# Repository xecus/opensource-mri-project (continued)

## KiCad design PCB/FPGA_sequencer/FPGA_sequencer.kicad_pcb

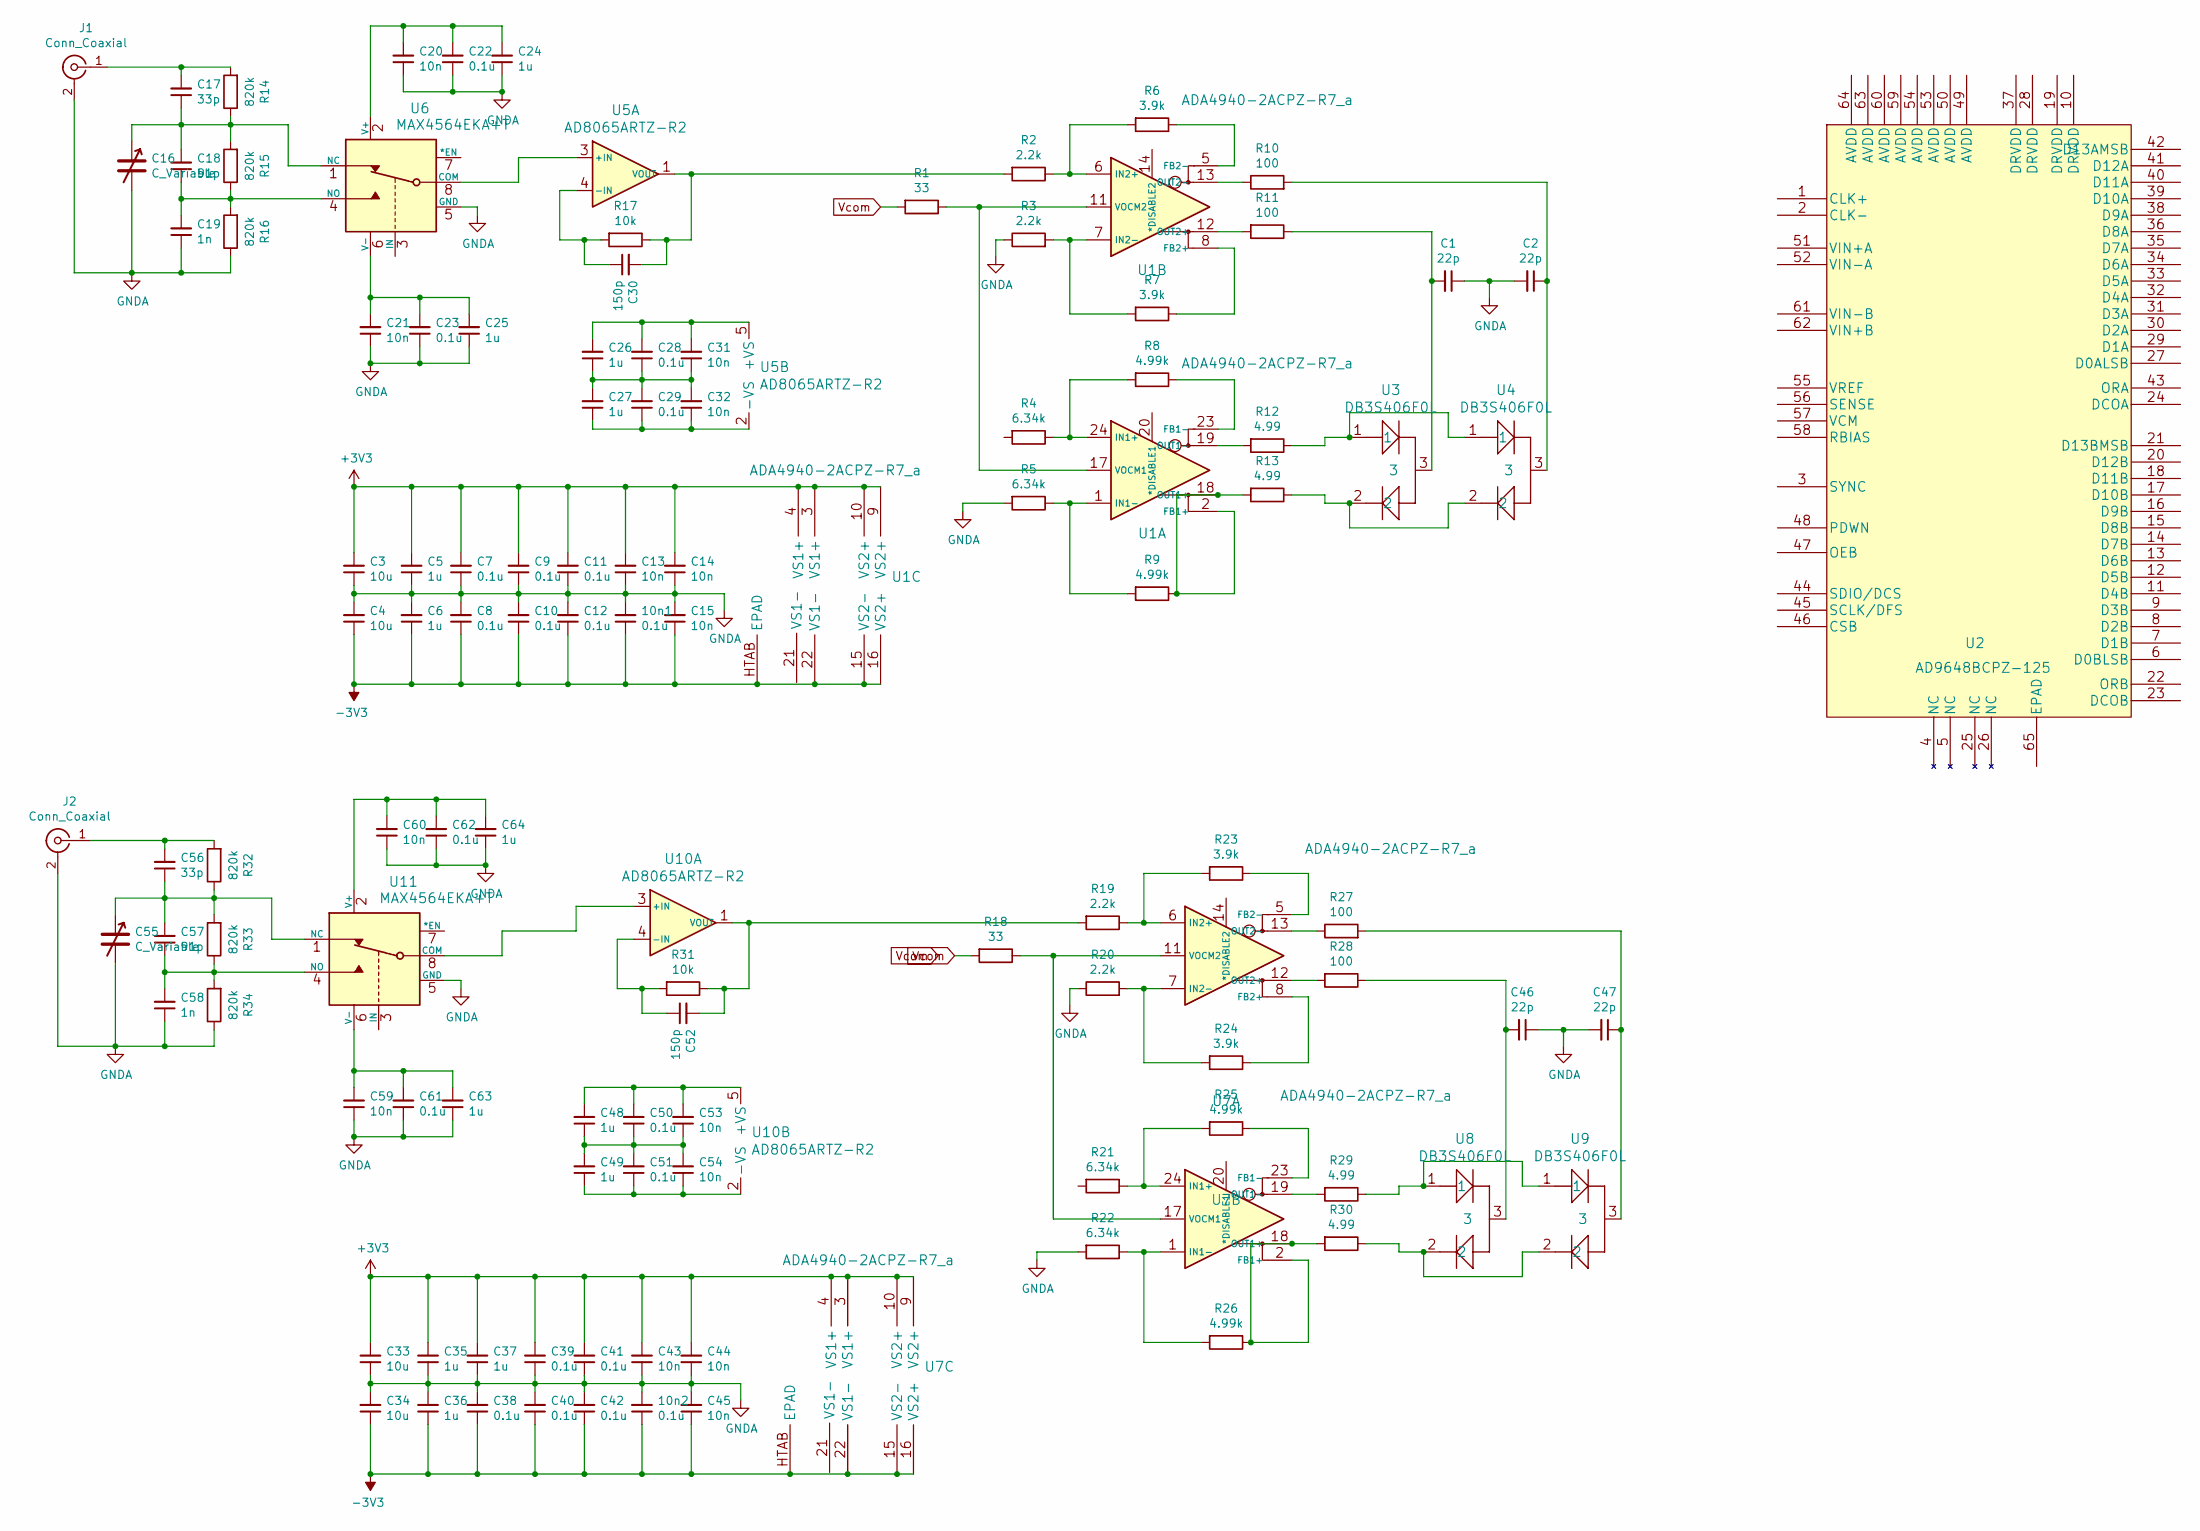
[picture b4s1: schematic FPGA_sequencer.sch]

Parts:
10n1, 10n2: 0.1u; C_0402_1005Metric
C1, C2, C46, C47: 22p; C_0402_1005Metric
C3, C4, C33, C34: 10u; C_0402_1005Metric
C5, C6, C24, C25, C26, C27, C35, C36, C37, C48, C49, C63, C64: 1u; C_0402_1005Metric
C7, C8, C9, C10, C11, C12, C22, C23, C28, C29, C38, C39, C40, C41, C42, C50, C51, C61, C62: 0.1u; C_0402_1005Metric
C13, C14, C15, C20, C21, C31, C32, C43, C44, C45, C53, C54, C59, C60: 10n; C_0402_1005Metric
C16, C55: C_Variable; C_Trimmer_Murata_TZB4-A
C17, C56: 33p; C_0402_1005Metric
C18, C57: 91p; C_0402_1005Metric
C19, C58: 1n; C_0402_1005Metric
C30, C52: 150p; C_0402_1005Metric
J1, J2: Conn_Coaxial; SMA_Amphenol_132134-11_Vertical
R1, R18: 33; R_0402_1005Metric
R2, R3, R19, R20: 2.2k; R_0402_1005Metric
R4, R5, R21, R22: 6.34k; R_0402_1005Metric
R6, R7, R23, R24: 3.9k; R_0402_1005Metric
R8, R9, R25, R26: 4.99k; R_0402_1005Metric
R10, R11, R27, R28: 100; R_0402_1005Metric
R12, R13, R29, R30: 4.99; R_0402_1005Metric
R14, R15, R16, R32, R33, R34: 820k; R_0402_1005Metric
R17, R31: 10k; R_0402_1005Metric
U1, U7: ADA4940-2ACPZ-R7_a; ADA4940-2ACPZ-R7
U2: AD9648BCPZ-125
U3, U4, U8, U9: DB3S406F0L
U5, U10: AD8065ARTZ-R2
U6, U11: MAX4564EKA+T; MAX4564EKA&plus_T

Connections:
+3V3: C3.2, C5.2, C7.2, C9.2, C11.2, C13.2, C14.2, C33.2, C35.2, C37.2, C39.2, C41.2, C43.2, C44.2, U1.3 (VS1+), U1.4 (VS1+), U1.9 (VS2+), U1.10 (VS2+), U7.3 (VS1+), U7.4 (VS1+), U7.9 (VS2+), U7.10 (VS2+)
-3V3: 10n1.1, 10n2.1, C4.1, C6.1, C8.1, C10.1, C12.1, C15.1, C34.1, C36.1, C38.1, C40.1, C42.1, C45.1, U1.15 (VS2-), U1.16 (VS2+), U1.22 (VS1-), U1.HTAB (EPAD), U7.15 (VS2-), U7.16 (VS2+), U7.22 (VS1-), U7.HTAB (EPAD)
GNDA: 10n1.2, 10n2.2, C1.1, C2.2, C3.1, C4.2, C5.1, C6.2, C7.1, C8.2, C9.1, C10.2, C11.1, C12.2, C13.1, C14.1, C15.2, C16.2, C19.1, C20.1, C21.1, C22.1, C23.1, C24.1, C25.1, C33.1, C34.2, C35.1, C36.2, C37.1, C38.2, C39.1, C40.2, C41.1, C42.2, C43.1, C44.1, C45.2, C46.1, C47.2, C55.2, C58.1, C59.1, C60.1, C61.1, C62.1, C63.1, C64.1, J1.2 (Ext), J2.2 (Ext), R3.1, R5.2, R16.1, R20.1, R22.2, R34.1, U6.5 (GND), U11.5 (GND)
unnamed: C1.2, R11.1, U3.3
unnamed: C2.1, R10.2, U4.3
unnamed: C16.1, C17.1, C18.2, R14.1, R15.2, U6.1 (NC)
unnamed: C17.2, J1.1 (In), R14.2
unnamed: C18.1, C19.2, R15.1, R16.2, U6.4 (NO)
unnamed: C20.2, C22.2, C24.2, U6.2 (V+)
unnamed: C21.2, C23.2, C25.2, U6.6 (V-)
unnamed: C26.1, C27.2, C28.1, C29.2, C31.1, C32.2
unnamed: C26.2, C28.2, C31.2, U5.5 (+VS)
unnamed: C27.1, C29.1, C32.1, U5.2 (-VS)
unnamed: C30.1, R17.2, U5.4 (-IN)
unnamed: C30.2, R2.2, R17.1, U5.1 (VOUT)
unnamed: C46.2, R28.1, U8.3
unnamed: C47.1, R27.2, U9.3
unnamed: C48.1, C49.2, C50.1, C51.2, C53.1, C54.2
unnamed: C48.2, C50.2, C53.2, U10.5 (+VS)
unnamed: C49.1, C51.1, C54.1, U10.2 (-VS)
unnamed: C52.1, R31.2, U10.4 (-IN)
unnamed: C52.2, R19.2, R31.1, U10.1 (VOUT)
unnamed: C55.1, C56.1, C57.2, R32.1, R33.2, U11.1 (NC)
unnamed: C56.2, J2.1 (In), R32.2
unnamed: C57.1, C58.2, R33.1, R34.2, U11.4 (NO)
unnamed: C59.2, C61.2, C63.2, U11.6 (V-)
unnamed: C60.2, C62.2, C64.2, U11.2 (V+)
unnamed: R1.1, U1.11 (VOCM2), U1.17 (VOCM1)
unnamed: R2.1, R6.2, U1.6 (IN2+)
unnamed: R3.2, R7.2, U1.7 (IN2-)
unnamed: R4.1, R8.2, U1.24 (IN1+)
unnamed: R5.1, R9.2, U1.1 (IN1-)
unnamed: R6.1, U1.5 (FB2-)
unnamed: R7.1, U1.8 (FB2+)
unnamed: R8.1, U1.23 (FB1-)
unnamed: R10.1, U1.13 (OUT2-)
unnamed: R11.2, U1.12 (OUT2+)
unnamed: R12.1, U3.1, U4.1
unnamed: R12.2, U1.19 (OUT1-)
unnamed: R13.1, U3.2, U4.2
unnamed: R9.1, R13.2, U1.2 (FB1+), U1.18 (OUT1+)
unnamed: R18.1, U7.11 (VOCM2), U7.17 (VOCM1)
unnamed: R19.1, R23.2, U7.6 (IN2+)
unnamed: R20.2, R24.2, U7.7 (IN2-)
unnamed: R21.1, R25.2, U7.24 (IN1+)
unnamed: R22.1, R26.2, U7.1 (IN1-)
unnamed: R23.1, U7.5 (FB2-)
unnamed: R24.1, U7.8 (FB2+)
unnamed: R25.1, U7.23 (FB1-)
unnamed: R26.1, R30.2, U7.2 (FB1+), U7.18 (OUT1+)
unnamed: R27.1, U7.13 (OUT2-)
unnamed: R28.2, U7.12 (OUT2+)
unnamed: R29.1, U8.1, U9.1
unnamed: R29.2, U7.19 (OUT1-)
unnamed: R30.1, U8.2, U9.2
unnamed: U5.3 (+IN), U6.8 (COM)
unnamed: U10.3 (+IN), U11.8 (COM)
Vcom: R1.2, R18.2

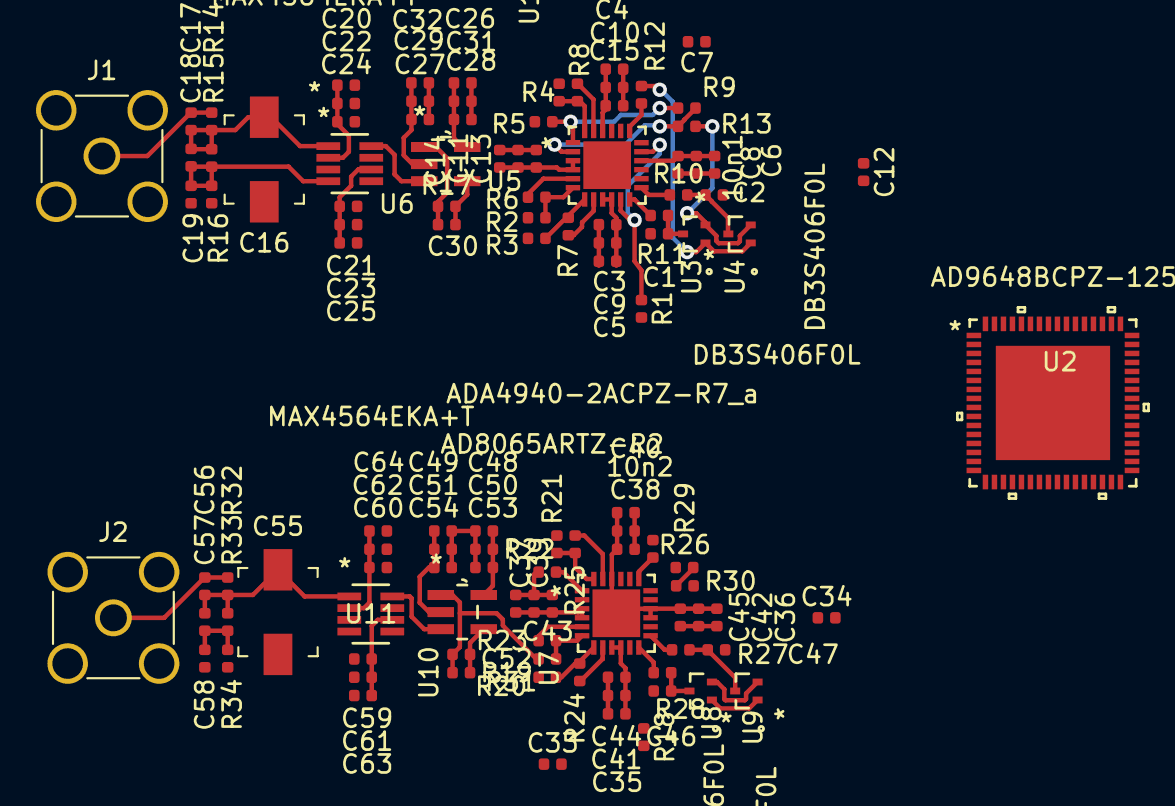
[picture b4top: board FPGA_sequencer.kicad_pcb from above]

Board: 2 copper layers, 113 parts (0 on the bottom side), 58 nets.

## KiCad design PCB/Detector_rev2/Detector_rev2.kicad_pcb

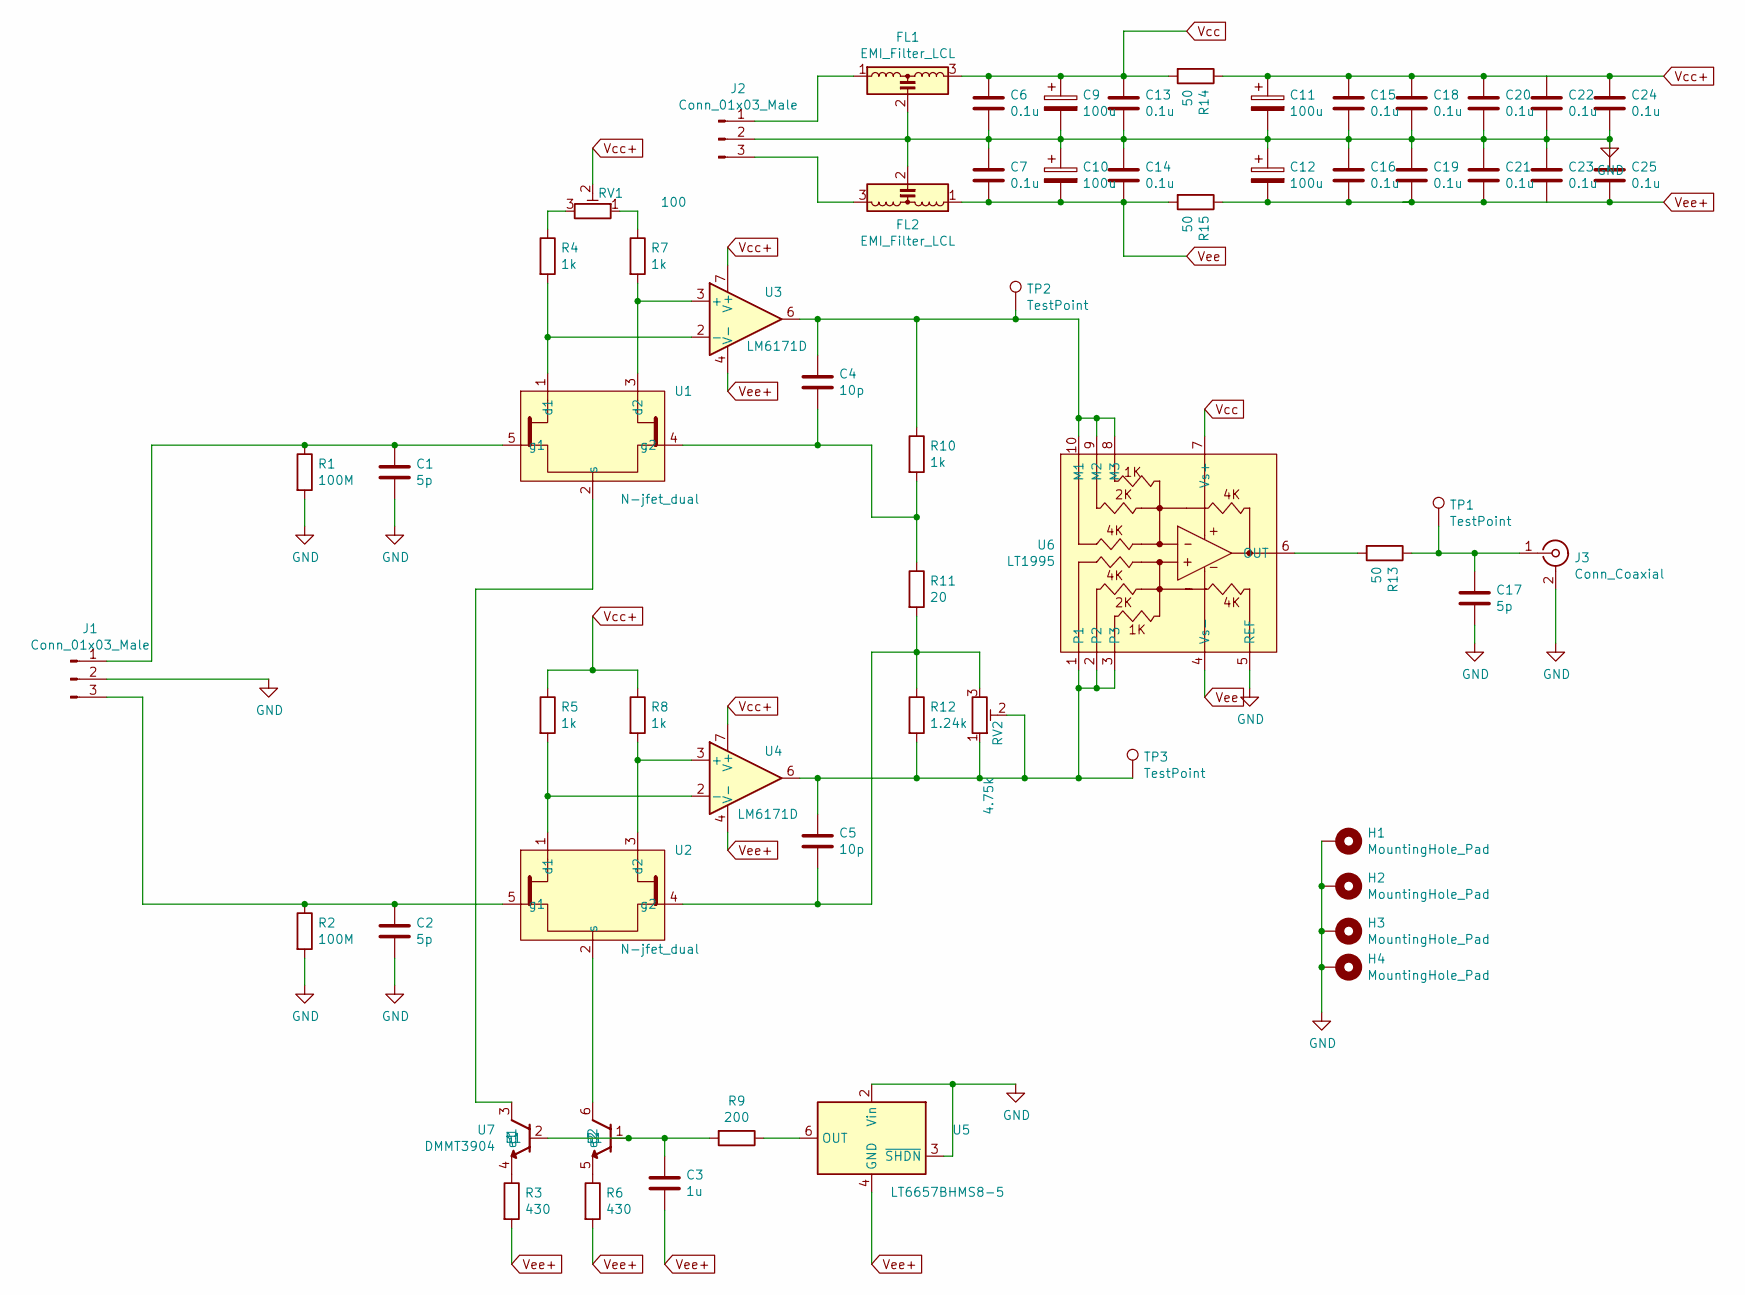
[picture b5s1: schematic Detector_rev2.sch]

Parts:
C1, C2, C17: 5p; C_0603_1608Metric
C3: 1u; C_0603_1608Metric
C4, C5: 10p; C_0603_1608Metric
C6, C7, C13, C14, C15, C16, C18, C19, C20, C21, C22, C23, C24, C25: 0.1u; C_0603_1608Metric
C9, C10, C11, C12: 100u; C_Elec_5x5.8
FL1, FL2: EMI_Filter_LCL; EMI_Filter_2606
H1, H2, H3, H4: MountingHole_Pad; MountingHole_2.7mm_Pad_Via
J1: Conn_01x03_Male; input
J2: Conn_01x03_Male; JST-XH_S3B
J3: Conn_Coaxial; SMA_Amphenol_132134_Vertical
R1, R2: 100M; R_0603_1608Metric
R3, R6: 430; R_0603_1608Metric
R4, R5, R7, R8, R10: 1k; R_0603_1608Metric
R9: 200; R_0603_1608Metric
R11: 20; R_0603_1608Metric
R12: 1.24k; R_0603_1608Metric
R13, R14, R15: 50; R_0603_1608Metric
RV1: 100; Potentiometer_Bourns_3269W_Vertical
RV2: 4.75k; Potentiometer_Bourns_3269W_Vertical
TP1, TP2, TP3: TestPoint; HK-1-G
U1, U2: N-jfet_dual; SOT_25
U3, U4: LM6171D; SOIC-8_3.9x4.9mm_P1.27mm
U5: LT6657BHMS8-5; MSOP-8_3x3mm_P0.65mm
U6: LT1995; MSOP-10_3x3mm_P0.5mm
U7: DMMT3904; SOT-363_SC-70-6

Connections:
GND: C1.2, C2.2, C6.2, C7.1, C9.2, C10.1, C11.2, C12.1, C13.2, C14.1, C15.2, C16.1, C17.2, C18.2, C19.1, C20.2, C21.1, C22.2, C23.1, C24.2, C25.1, FL1.2, FL2.2, H1.1, H2.1, H3.1, H4.1, J1.2, J2.2, J3.2 (Ext), R1.2, R2.2, U5.2 (Vin), U5.3 (~SHDN), U6.5 (REF)
unnamed: C1.1, J1.1, R1.1, U1.5 (g1)
unnamed: C2.1, J1.3, R2.1, U2.5 (g1)
unnamed: C3.2, R9.2, U7.1 (b1), U7.2 (b1)
unnamed: C4.1, R10.1, TP2.1, U3.6, U6.8 (M3), U6.9 (M2), U6.10 (M1)
unnamed: C4.2, R10.2, R11.1, U1.4 (g2)
unnamed: C5.1, R12.2, RV2.1, RV2.2, TP3.1, U4.6, U6.1, U6.2, U6.3
unnamed: C5.2, R11.2, R12.1, RV2.3, U2.4 (g2)
unnamed: C17.1, J3.1 (In), R13.1, TP1.1
unnamed: FL1.1, J2.1
unnamed: FL2.3, J2.3
unnamed: R3.1, U7.4 (e1)
unnamed: R4.1, RV1.3
unnamed: R4.2, U1.1 (d1), U3.2 (-)
unnamed: R5.2, U2.1 (d1), U4.2 (-)
unnamed: R6.1, U7.5 (e2)
unnamed: R7.1, RV1.1
unnamed: R7.2, U1.3 (d2), U3.3 (+)
unnamed: R8.2, U2.3 (d2), U4.3 (+)
unnamed: R9.1, U5.6 (OUT)
unnamed: R13.2, U6.6 (OUT)
unnamed: U1.2 (s), U7.3 (c1)
unnamed: U2.2 (s), U7.6 (c2)
Vcc: C6.1, C9.1, C13.1, FL1.3, R14.2, U6.7 (Vs+)
Vcc+: C11.1, C15.1, C18.1, C20.1, C22.1, C24.1, R5.1, R8.1, R14.1, RV1.2, U3.7 (V+), U4.7 (V+)
Vee: C7.2, C10.2, C14.2, FL2.1, R15.2, U6.4 (Vs-)
Vee+: C3.1, C12.2, C16.2, C19.2, C21.2, C23.2, C25.2, R3.2, R6.2, R15.1, U3.4 (V-), U4.4 (V-), U5.4 (GND)

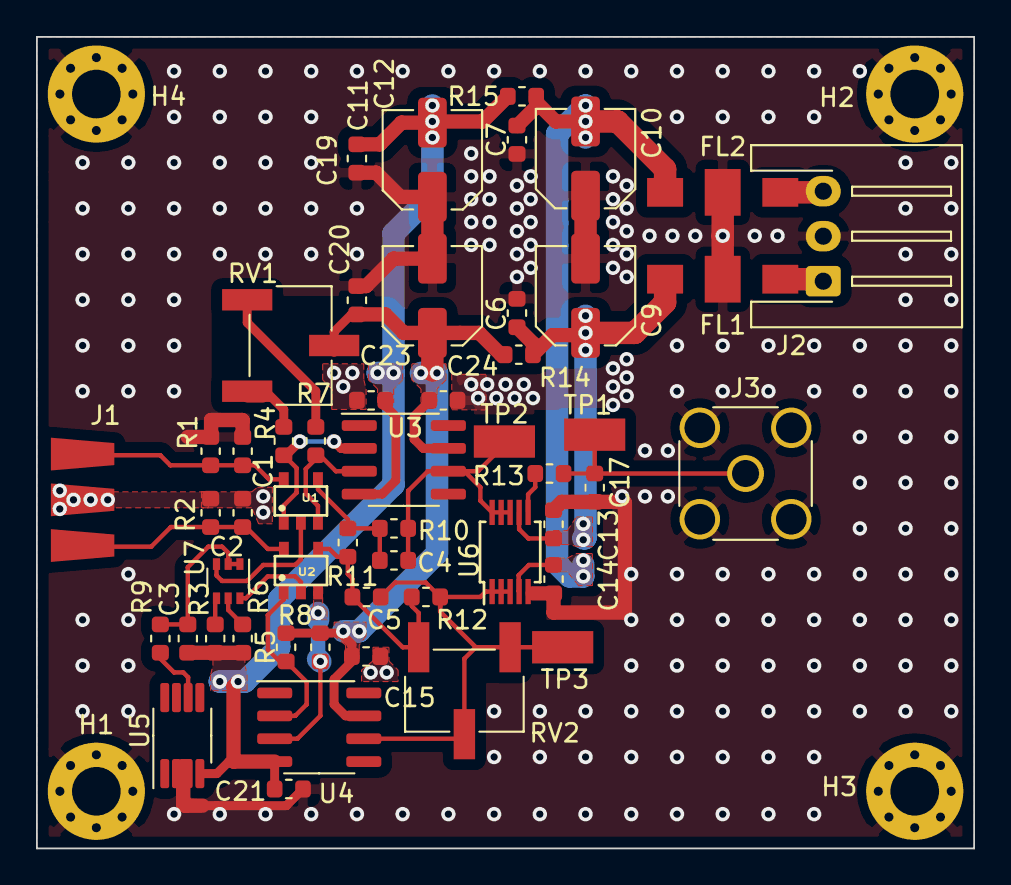
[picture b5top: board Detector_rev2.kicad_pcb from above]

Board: 2 copper layers, 52.1 x 45.1 mm, 56 parts (0 on the bottom side), 27 nets.

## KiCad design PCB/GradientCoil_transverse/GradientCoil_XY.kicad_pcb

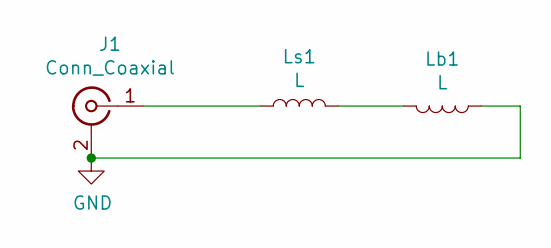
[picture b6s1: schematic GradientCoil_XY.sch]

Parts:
J1: Conn_Coaxial; SMA_Amphenol_132134-16_Vertical
Lb1: L; GC_XY_bottom_r6
Ls1: L; GC_XY_surf_r1

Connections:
GND: J1.2 (Ext), Lb1.1
unnamed: J1.1 (In), Ls1.1
unnamed: Lb1.2, Ls1.2

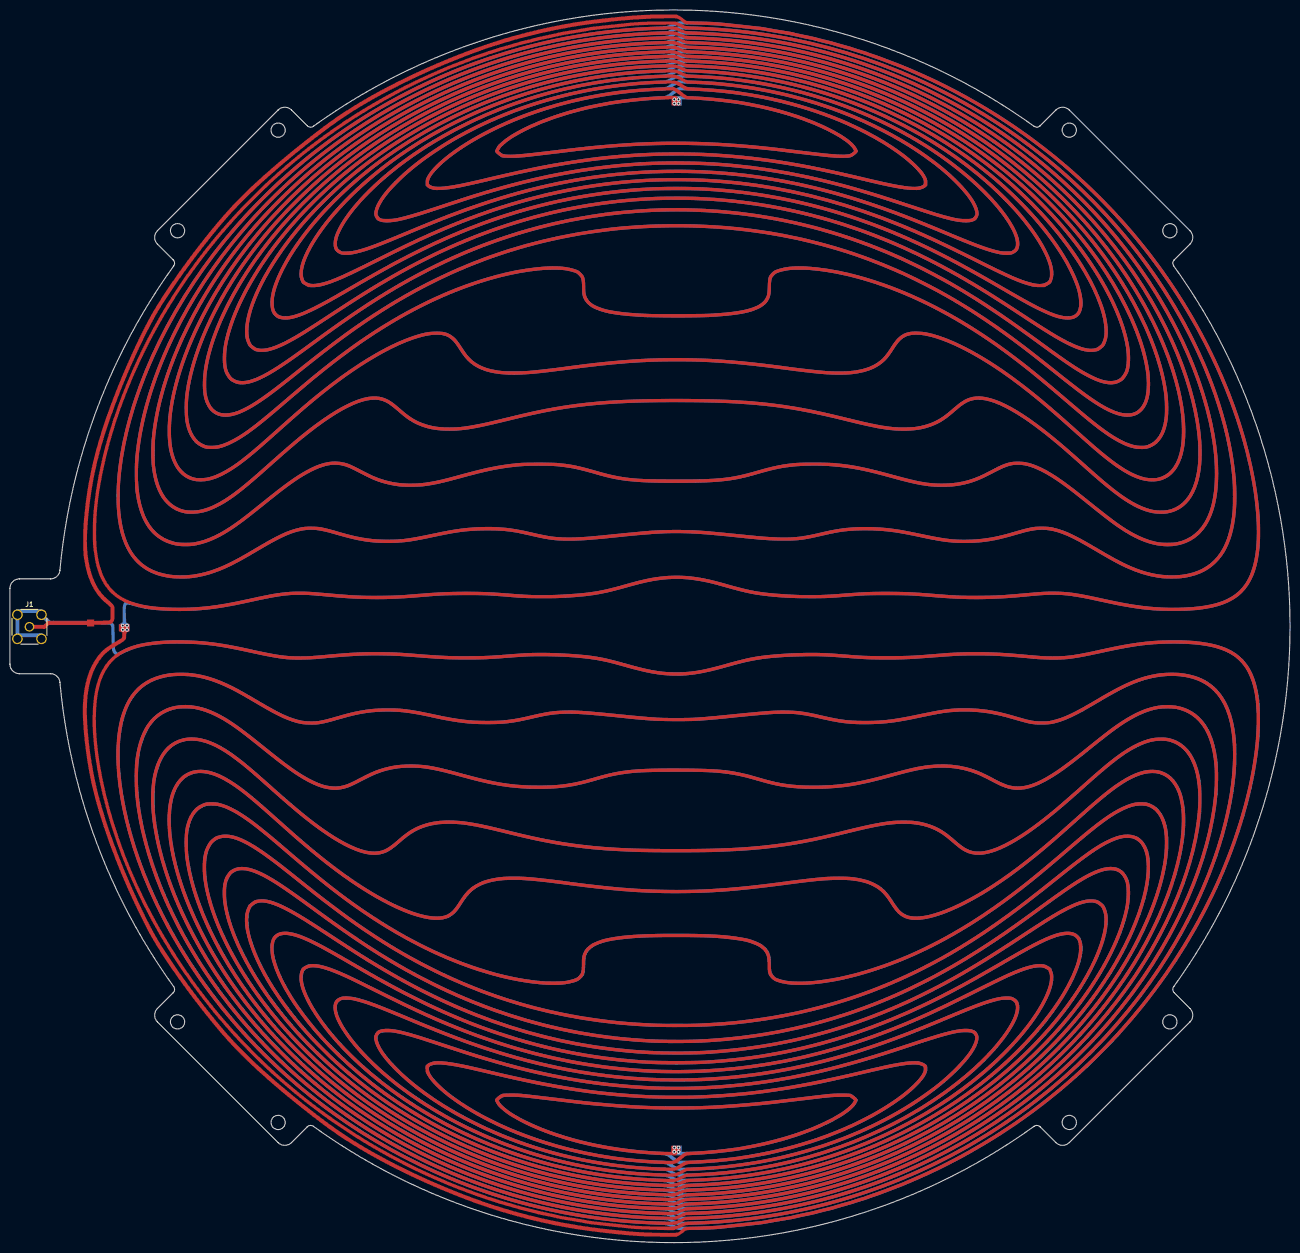
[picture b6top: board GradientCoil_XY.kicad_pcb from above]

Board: 2 copper layers, 270.0 x 260.0 mm, 3 parts (0 on the bottom side), 3 nets.

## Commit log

2020-04-10 Create Detector
2020-04-10 Create note
2020-04-10 横方向勾配コイルフォルダの作成
2020-04-10 Update and rename Detector to PCB_note
2020-04-11 pass capacitor add
2020-04-12 AD8065 add
2020-04-12 MAX4565 Analog switch add
2020-04-13 input terminal adjust
2020-04-14 garberdata output
2020-04-16 ADC driver pattern write
2020-05-16 Current Controller and GradientDriver_rev2
2020-05-16 GradDriver rev2 edit
